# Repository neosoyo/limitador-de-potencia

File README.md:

# Limitador de Potência
Dispositivo para medição de potência e consumo com controlador de limitador de potência para propulsão elétrica de Aeronaves rádio controladas.

# Configurador

Aplicativo para visualização de daods e ajustes da malha de controle.

# Hardware
Utiliza MCU nrf52 (xiao ble), com os seguintes periféricos:

| Periférico | Descrição |
|---|---|
| INA226 | Leitor de corrente, tensão e potência, R shunt de 50mOhms |
| SK6812mini | Led rgba para indicão de status |
| Saída PWM | com BSS138 para ajuste de nível lógico em 5Vdc |
| Entrada PWM | com BSS138 para ajuste de nível lógico para 3.3Vdc |
| Saída UART | 115200 bps, saída de dados em tempo real do control | 
| BLE | Transmissão de informações me tempo real via BLE |

# Firmware

Metas:

* Executar limitação de potência regulando sinal PWM utilizando mensurações do INA226 e uma malha de controle to tipo ADRC.
* Fornecer Potência, Tensão, Corrente, Energia Consumida e sinais PWMs (entrada, controle e saída) pela porta UART.
* Permitir a configuração de número de idenficação e ajuste da malha de controle pela porta USB.
* Através de comunicação bluetooth BLE, transmitir tempo total ligado em segundos, potência máxima, número de identificação e acumulado de energia consumida.
* Suportar bootloader com assinatura de firmware.

# Futuro

Adicionar um monitor de células da bateria: https://www.analog.com/media/en/technical-documentation/data-sheets/ltc6810-1-6810-2.pdf

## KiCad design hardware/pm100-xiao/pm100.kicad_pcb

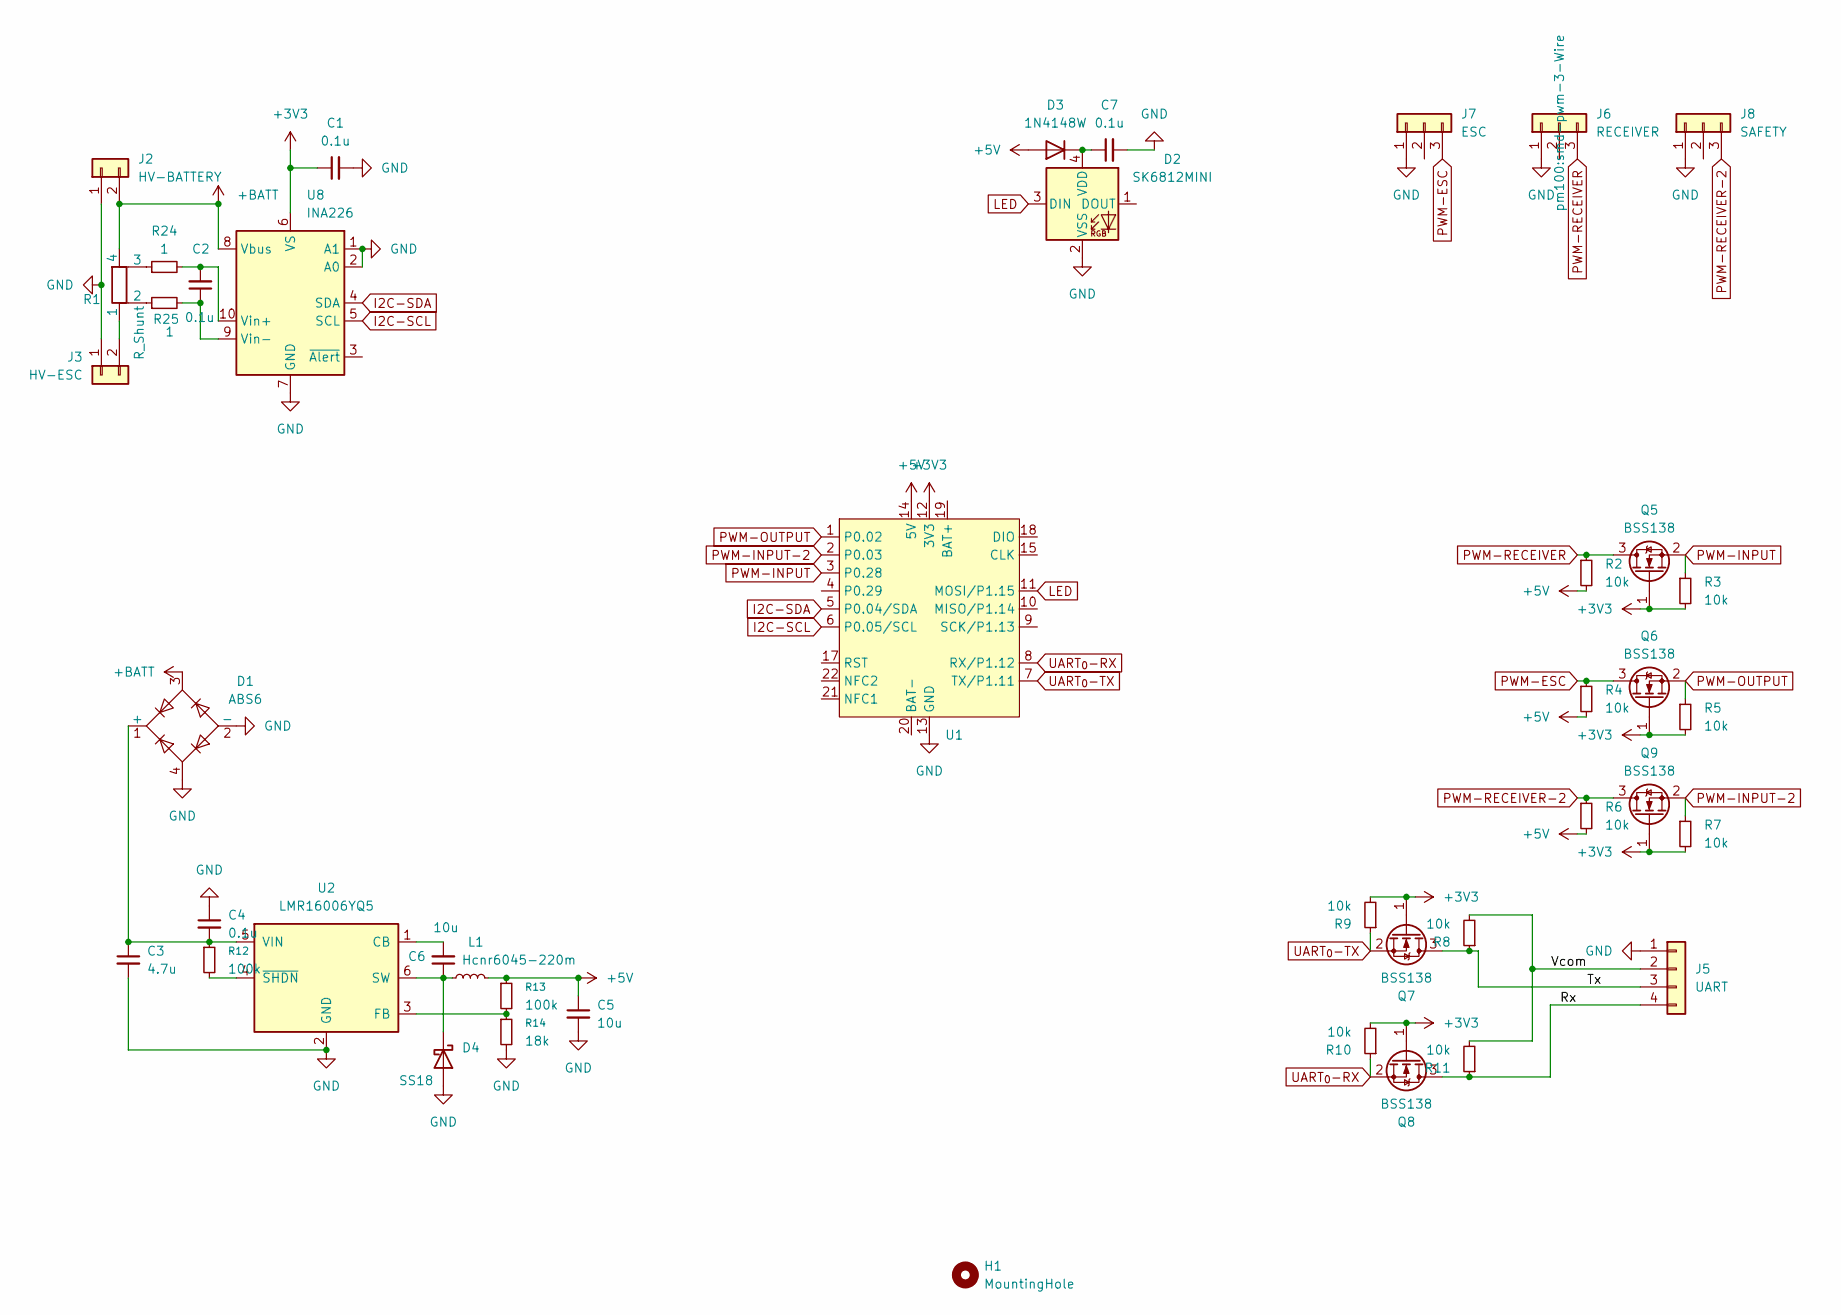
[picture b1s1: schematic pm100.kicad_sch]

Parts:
C1, C2, C7: 0.1u; C_0603_1608Metric
C3: 4.7u; C_0805_2012Metric
C4: 0.1u; C_0805_2012Metric
C5, C6: 10u; C_0805_2012Metric
D1: ABS6; Diode_Bridge_Diotec_ABS
D2: SK6812MINI; SK6812MINI-E
D3: 1N4148W; D_SOD-123
D4: SS18; D_SMA
H1: MountingHole; MountingHole_3.2mm_M3_ISO7380
J2: HV-BATTERY; AMASS_XT60IPW-M_1x03_P7.20mm_Horizontal
J3: HV-ESC; AMASS_XT60PW-F_1x02_P7.20mm_Horizontal
J5: UART; Hirose_DF13-04P-1.25DS_1x04_P1.25mm_Horizontal
J6: RECEIVER; smd-pwm-3-Wire
J7: ESC; smd-pwm-3-Wire
J8: SAFETY; smd-pwm-3-Wire
L1: Hcnr6045-220m; L_Bourns_SRN6045TA
Q5, Q6, Q7, Q8, Q9: BSS138; SOT-23
R1: R_Shunt; MSRSF3920P
R2, R3, R4, R5, R6, R7, R8, R9, R10, R11: 10k; R_0603_1608Metric
R12, R13: 100k; R_0603_1608Metric
R14: 18k; R_0603_1608Metric
R24, R25: 1; R_0603_1608Metric
U1: Xiao_BLE_sense
U2: LMR16006YQ5; SOT-23-6
U8: INA226; VSSOP-10_3x3mm_P0.5mm

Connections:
+3V3: C1.1, Q5.1 (G), Q6.1 (G), Q7.1 (G), Q8.1 (G), Q9.1 (G), R3.2, R5.2, R7.2, R9.2, R10.2, U1.12 (3V3), U8.6 (VS)
+5V: C5.1, D3.2 (A), L1.2, R2.2, R4.2, R6.2, R13.1, U1.14 (5V)
+BATT: D1.3, J2.2, R1.4, U8.8 (Vbus)
/Rx: J5.4, Q8.3 (D), R11.1
/Tx: J5.3, Q7.3 (D), R8.1
/Vcom: J5.2, R8.2, R11.2
GND: C1.2, C3.2, C4.1, C5.2, C7.2, D1.2 (-), D1.4, D2.2 (VSS), D4.2 (A), J2.1, J3.1, J5.1, J6.1, J7.1, J8.1, R14.2, U1.13 (GND), U1.16 (GND), U2.2 (GND), U8.1 (A1), U8.2 (A0), U8.7 (GND)
I2C-SCL: U1.6 (P0.05/SCL), U8.5 (SCL)
I2C-SDA: U1.5 (P0.04/SDA), U8.4 (SDA)
LED: D2.3 (DIN), U1.11 (MOSI/P1.15)
unnamed: C3.1, C4.2, D1.1 (+), R12.1, U2.5 (VIN)
unnamed: C7.1, D2.4 (VDD), D3.1 (K)
unnamed: C6.1, D4.1 (K), L1.1, U2.6 (SW)
unnamed: J3.2, R1.1
unnamed: R1.2, R25.1
unnamed: R1.3, R24.1
unnamed: C6.2, U2.1 (CB)
unnamed: R13.2, R14.1, U2.3 (FB)
unnamed: R12.2, U2.4 (~SHDN)
unnamed: C2.2, R24.2, U8.10 (Vin+)
unnamed: C2.1, R25.2, U8.9 (Vin-)
PWM-ESC: J7.3, Q6.3 (D), R4.1
PWM-INPUT: Q5.2 (S), R3.1, U1.3 (P0.28)
PWM-INPUT-2: Q9.2 (S), R7.1, U1.2 (P0.03)
PWM-OUTPUT: Q6.2 (S), R5.1, U1.1 (P0.02)
PWM-RECEIVER: J6.3, Q5.3 (D), R2.1
PWM-RECEIVER-2: J8.3, Q9.3 (D), R6.1
UART_{0}-RX: Q8.2 (S), R10.1, U1.8 (RX/P1.12)
UART_{0}-TX: Q7.2 (S), R9.1, U1.7 (TX/P1.11)

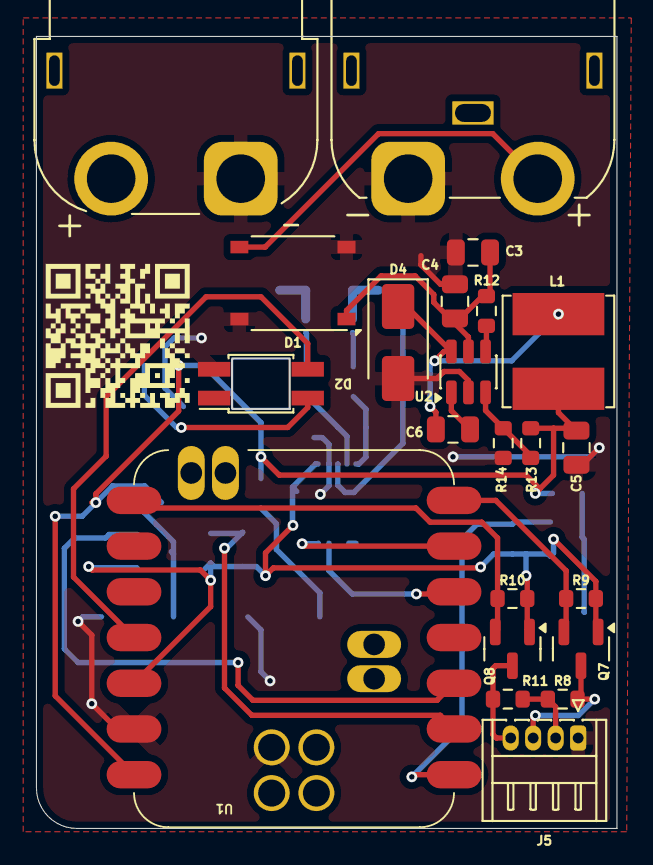
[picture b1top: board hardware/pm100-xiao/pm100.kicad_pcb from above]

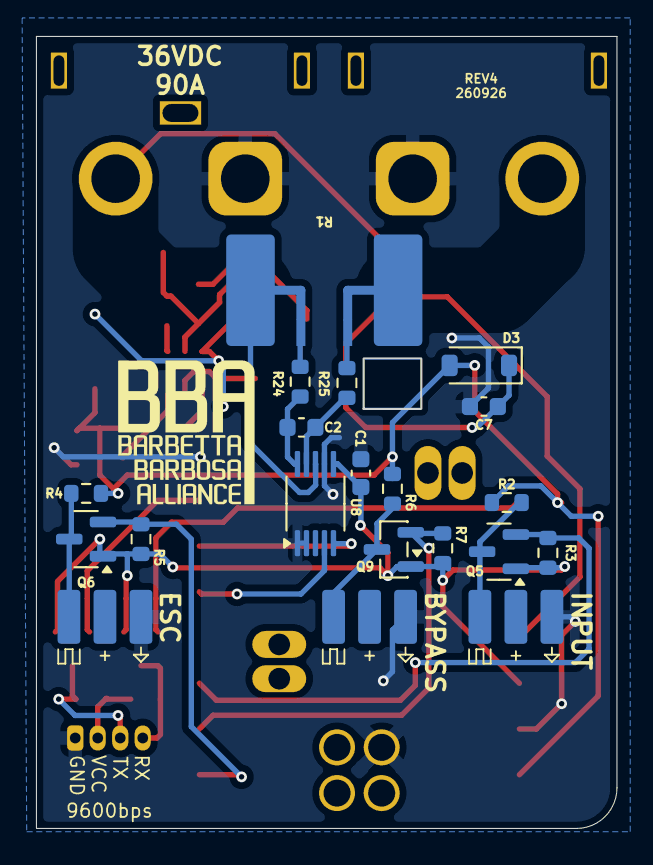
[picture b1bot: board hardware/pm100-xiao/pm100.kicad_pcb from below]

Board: 2 copper layers, 32.2 x 43.9 mm, 42 parts (20 on the bottom side), 29 nets.

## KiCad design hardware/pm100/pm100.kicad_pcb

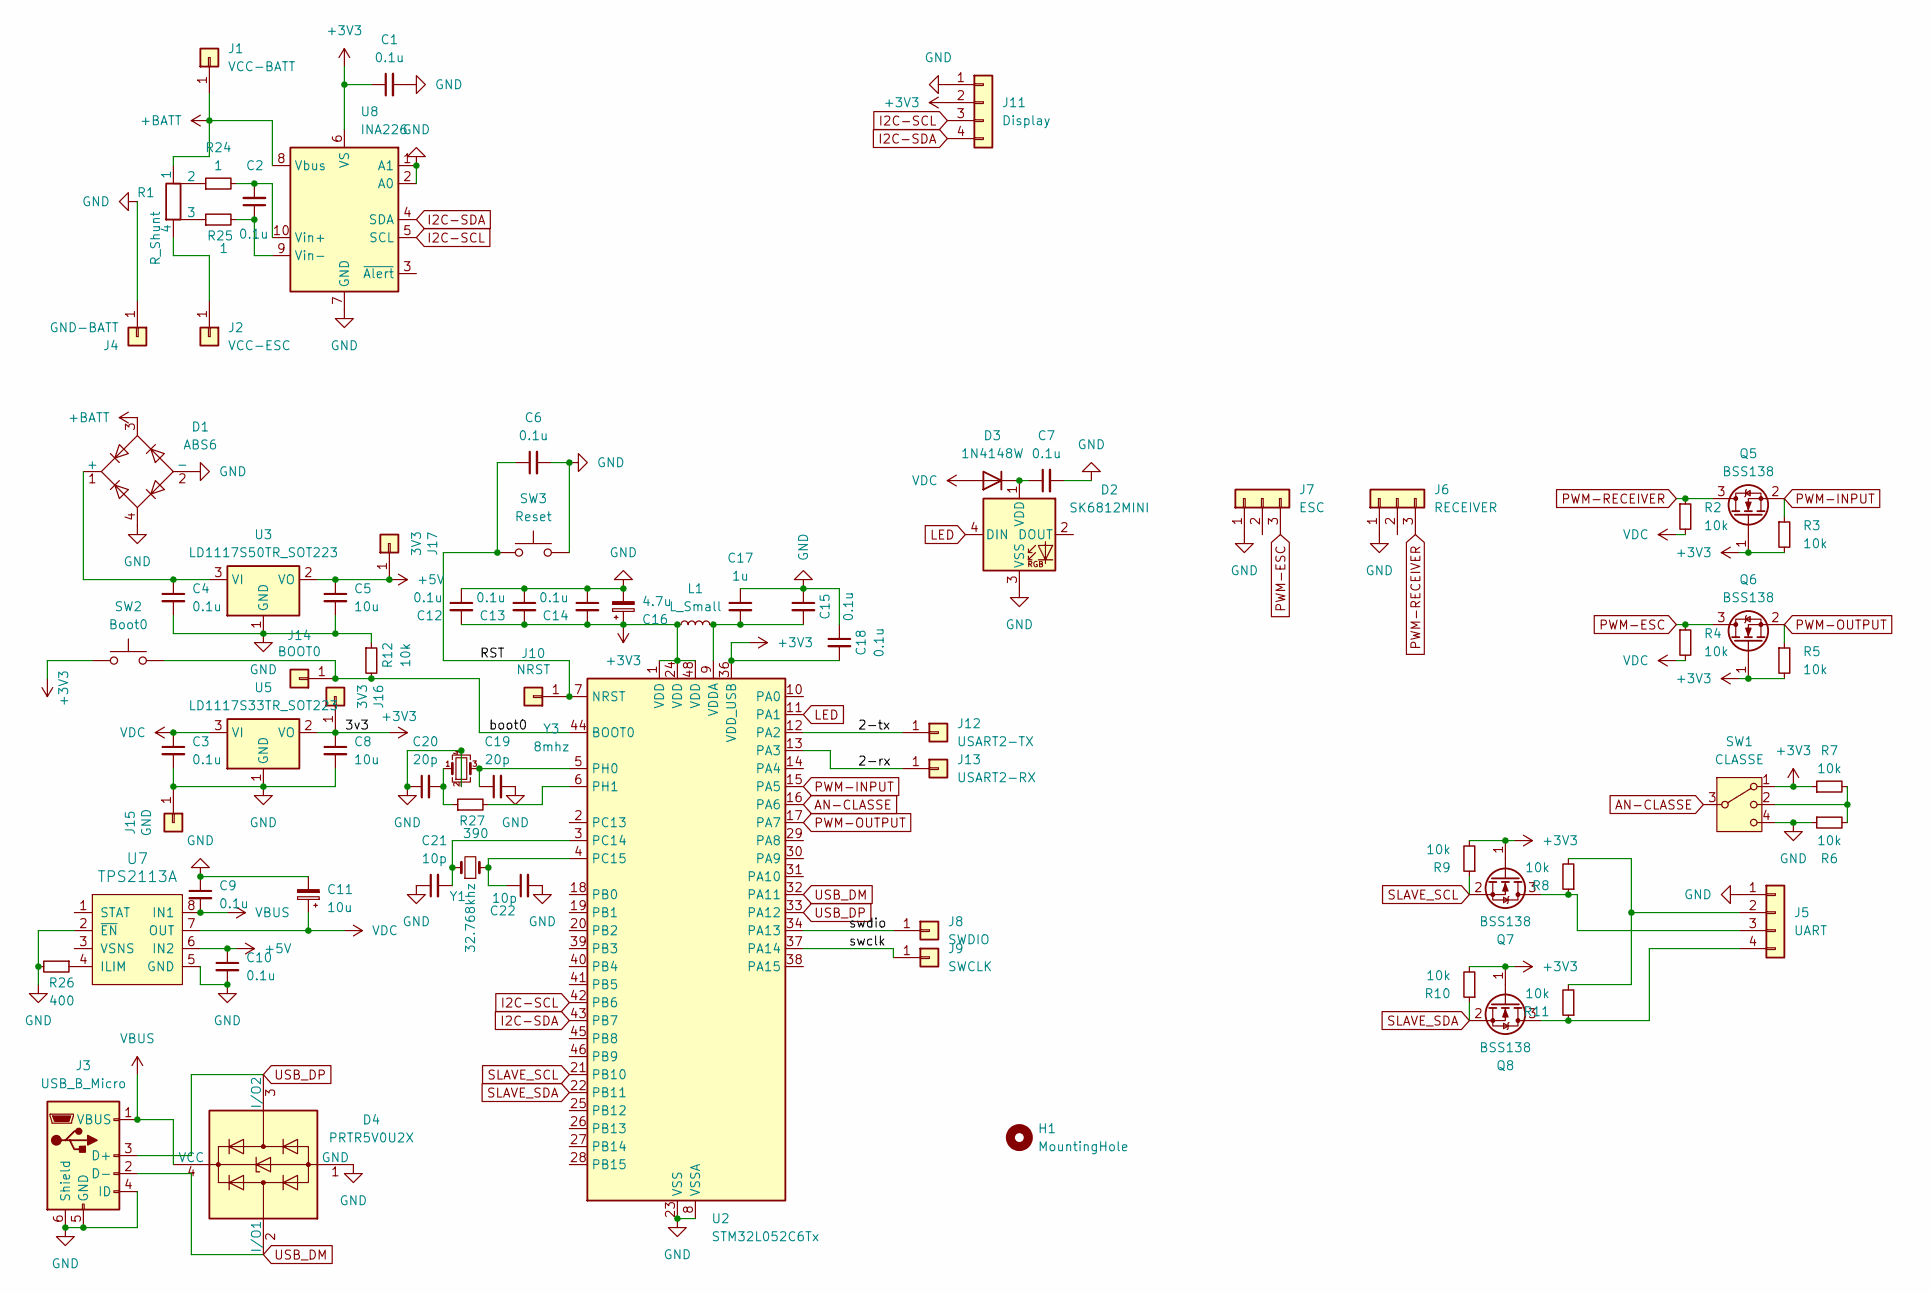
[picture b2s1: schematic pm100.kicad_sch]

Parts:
C1, C2, C3, C4, C6, C7, C9, C10, C12, C13, C14, C15, C18: 0.1u; C_0603_1608Metric
C5, C8: 10u; C_0805_2012Metric
C11: 10u; CP_EIA-3528-21_Kemet-B
C16: 4.7u; CP_EIA-3216-18_Kemet-A
C17: 1u; C_0603_1608Metric
C19, C20: 20p; C_0603_1608Metric
C21, C22: 10p; C_0603_1608Metric
D1: ABS6; Diode_Bridge_Diotec_ABS
D2: SK6812MINI; SK6812MINI-E
D3: 1N4148W; D_SOD-123
D4: PRTR5V0U2X; SOT-143
H1: MountingHole; MountingHole_3.2mm_M3_ISO7380
J1: VCC-BATT; HV_CONN_01x01_pad_6.2x12mm
J2: VCC-ESC; HV_CONN_01x01_pad_6.2x12mm
J3: USB_B_Micro; 47589-1001
J4: GND-BATT; HV_CONN_01x01_pad_6.2x12mm
J5: UART; JST_XH_S4B-XH-A-1_1x04_P2.50mm_Horizontal
J6: RECEIVER; SolderWire_SMD_3
J7: ESC; SolderWire_SMD_3
J8: SWDIO; TestPoint_Pad_D2.0mm
J9: SWCLK; TestPoint_Pad_D2.0mm
J10: NRST; TestPoint_Pad_D2.0mm
J11: Display; OLED_0.91_128x32
J12: USART2-TX; TestPoint_Pad_D2.0mm
J13: USART2-RX; TestPoint_Pad_D2.0mm
J14: BOOT0; TestPoint_Pad_D2.0mm
J15: GND; TestPoint_Pad_D2.0mm
J16, J17: 3V3; TestPoint_Pad_D2.0mm
L1: L_Small; L_0603_1608Metric
Q5, Q6, Q7, Q8: BSS138; SOT-23
R1: R_Shunt; MSRSF3920P
R2, R3, R4, R5, R6, R7, R8, R9, R10, R11, R12: 10k; R_0603_1608Metric
R24, R25: 1; R_0603_1608Metric
R26: 400; R_0603_1608Metric
R27: 390; R_0603_1608Metric
SW1: CLASSE; SW_SP3T_PCM13
SW2: Boot0; SW_Tactile_SPST_NO_Straight_CK_PTS636Sx25SMTRLFS
SW3: Reset; SW_Tactile_SPST_NO_Straight_CK_PTS636Sx25SMTRLFS
U2: STM32L052C6Tx; LQFP-48_7x7mm_P0.5mm
U3: LD1117S50TR_SOT223; SOT-223-3_TabPin2
U5: LD1117S33TR_SOT223; SOT-223-3_TabPin2
U7: TPS2113A; TSSOP-8_3x3mm_P0.65mm
U8: INA226; VSSOP-10_3x3mm_P0.5mm
Y1: 32.768khz; Crystal_SMD_3215-2Pin_3.2x1.5mm
Y3: 8mhz; Crystal_SMD_3225-4Pin_3.2x2.5mm_HandSoldering

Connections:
+3V3: C1.1, C8.1, C12.2, C13.2, C14.2, C16.1, C18.2, J11.2, J16.1, L1.1, Q5.1 (G), Q6.1 (G), Q7.1 (G), Q8.1 (G), R3.2, R5.2, R7.1, R9.2, R10.2, SW1.1, SW2.1, U2.1 (VDD), U2.24 (VDD), U2.36 (VDD_USB), U2.48 (VDD), U5.2 (VO), U8.6 (VS)
+5V: C5.1, C10.1, J17.1, U3.2 (VO), U7.6 (IN2)
+BATT: D1.3, J1.1, R1.1, U8.8 (Vbus)
AN-CLASSE: SW1.3, U2.16 (PA6)
GND: C1.2, C3.2, C4.2, C5.2, C6.2, C7.2, C8.2, C9.1, C10.2, C11.2, C12.1, C13.1, C14.1, C15.1, C16.2, C17.1, C18.1, C19.2, C20.1, C21.1, C22.2, D1.2 (-), D1.4, D2.3 (VSS), D4.1 (GND), J3.4 (ID), J3.5 (GND), J3.6 (Shield), J4.1, J5.1, J6.1, J7.1, J11.1, J15.1, R6.1, R12.1, R26.2, SW1.4, SW3.2, U2.8 (VSSA), U2.23 (VSS), U2.35 (VSS), U2.47 (VSS), U3.1 (GND), U5.1 (GND), U7.2 (~EN), U7.5 (GND), U8.1 (A1), U8.2 (A0), U8.7 (GND), Y3.2, Y3.4
I2C-SCL: J11.3, U2.42 (PB6), U8.5 (SCL)
I2C-SDA: J11.4, U2.43 (PB7), U8.4 (SDA)
LED: D2.4 (DIN), U2.11 (PA1)
unnamed: C20.2, R27.1, Y3.1
unnamed: C4.1, D1.1 (+), U3.3 (VI)
unnamed: C7.1, D2.1 (VDD), D3.1 (K)
unnamed: J2.1, R1.4
unnamed: J5.2, R8.2, R11.2
unnamed: J5.3, Q7.3 (D), R8.1
unnamed: J5.4, Q8.3 (D), R11.1
unnamed: J8.1, U2.34 (PA13)
unnamed: J9.1, U2.37 (PA14)
unnamed: C6.1, J10.1, SW3.1, U2.7 (NRST)
unnamed: J12.1, U2.12 (PA2)
unnamed: J13.1, U2.13 (PA3)
unnamed: J14.1, R12.2, SW2.2, U2.44 (BOOT0)
unnamed: R1.2, R24.1
unnamed: R1.3, R25.1
unnamed: R6.2, R7.2, SW1.2
unnamed: C21.2, U2.3 (PC14), Y1.1
unnamed: C22.1, U2.4 (PC15), Y1.2
unnamed: C19.1, U2.5 (PH0), Y3.3
unnamed: R27.2, U2.6 (PH1)
unnamed: C15.2, C17.2, L1.2, U2.9 (VDDA)
unnamed: R26.1, U7.4 (ILIM)
unnamed: C2.2, R24.2, U8.10 (Vin+)
unnamed: C2.1, R25.2, U8.9 (Vin-)
PWM-ESC: J7.3, Q6.3 (D), R4.1
PWM-INPUT: Q5.2 (S), R3.1, U2.15 (PA5)
PWM-OUTPUT: Q6.2 (S), R5.1, U2.17 (PA7)
PWM-RECEIVER: J6.3, Q5.3 (D), R2.1
SLAVE_SCL: Q7.2 (S), R9.1, U2.21 (PB10)
SLAVE_SDA: Q8.2 (S), R10.1, U2.22 (PB11)
USB_DM: D4.2 (I/O1), J3.2 (D-), U2.32 (PA11)
USB_DP: D4.3 (I/O2), J3.3 (D+), U2.33 (PA12)
VBUS: C9.2, D4.4 (VCC), J3.1 (VBUS), U7.8 (IN1)
VDC: C3.1, C11.1, D3.2 (A), R2.2, R4.2, U5.3 (VI), U7.7 (OUT)

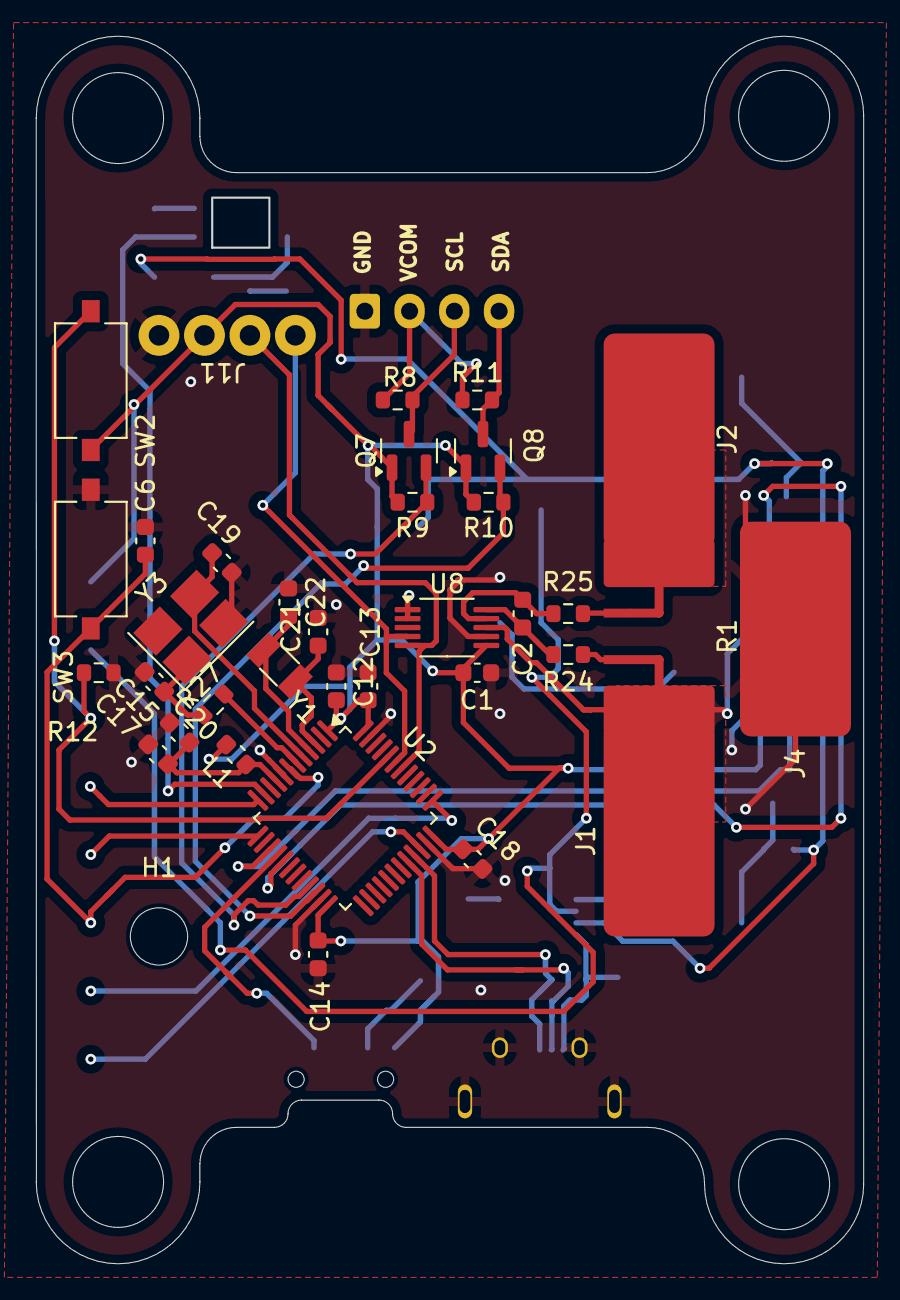
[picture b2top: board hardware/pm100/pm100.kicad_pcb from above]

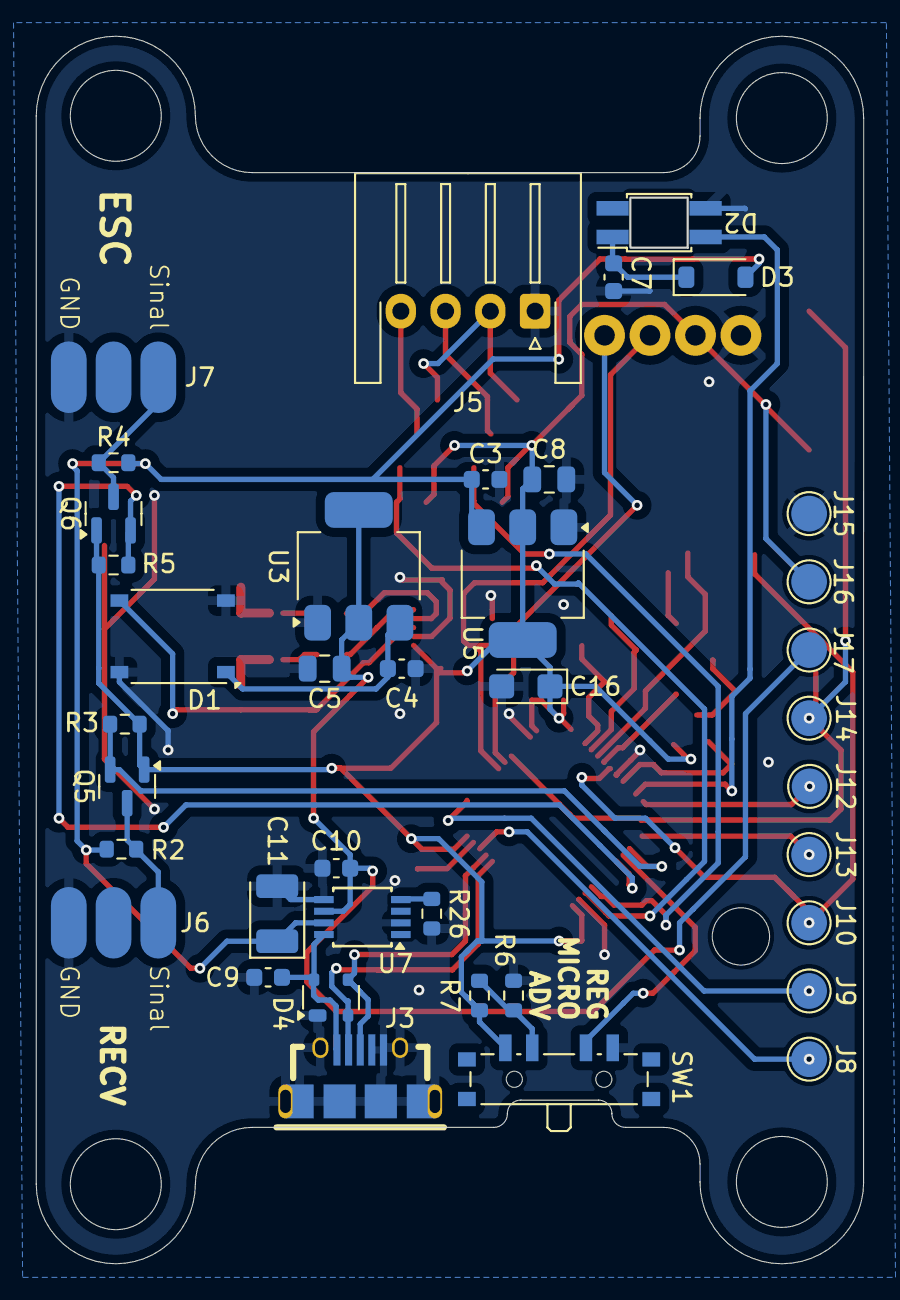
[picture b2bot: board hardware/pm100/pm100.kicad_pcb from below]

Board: 2 copper layers, 46.2 x 68.5 mm, 75 parts (39 on the bottom side), 42 nets.

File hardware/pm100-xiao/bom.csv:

"Reference","Value","Datasheet","Footprint","Qty","DNP"
"C1,C2,C3,C4,C7,C9,C10,C12,C13,C14,C15,C18","0.1u","~","Capacitor_SMD:C_0603_1608Metric","12",""
"C5,C8,C11","10u","~","-- mixed values --","3",""
"C16","4.7u","~","Capacitor_Tantalum_SMD:CP_EIA-3216-18_Kemet-A","1",""
"C17","1u","~","Capacitor_SMD:C_0603_1608Metric","1",""
"C19,C20","20p","~","Capacitor_SMD:C_0603_1608Metric","2",""
"C21,C22","10p","~","Capacitor_SMD:C_0603_1608Metric","2",""
"D1","ABS6","https://diotec.com/tl_files/diotec/files/pdf/datasheets/abs2.pdf","Diode_SMD:Diode_Bridge_Diotec_ABS","1",""
"D2","SK6812MINI","https://cdn-shop.adafruit.com/product-files/2686/SK6812MINI_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","Sigma Footprints:SK6812MINI-E","1",""
"D3","1N4148W","https://www.vishay.com/docs/85748/1n4148w.pdf","Diode_SMD:D_SOD-123","1",""
"D4","PRTR5V0U2X","https://assets.nexperia.com/documents/data-sheet/PRTR5V0U2X.pdf","Package_TO_SOT_SMD:SOT-143","1",""
"J1","VCC-BATT","~","footprints:HV_CONN_01x01_pad_6.2x12mm","1",""
"J2","VCC-ESC","~","footprints:HV_CONN_01x01_pad_6.2x12mm","1",""
"J3","USB_B_Micro","~","footprints:47589-1001","1",""
"J4","GND-BATT","~","footprints:HV_CONN_01x01_pad_6.2x12mm","1",""
"J5","UART","~","Connector_JST:JST_XH_S4B-XH-A-1_1x04_P2.50mm_Horizontal","1",""
"J6","RECEIVER","~","Sigma Footprints:SolderWire_SMD_3","1",""
"J7","ESC","~","Sigma Footprints:SolderWire_SMD_3","1",""
"J8","SWDIO","~","TestPoint:TestPoint_Pad_D2.0mm","1",""
"J9","SWCLK","~","TestPoint:TestPoint_Pad_D2.0mm","1",""
"J10","NRST","~","TestPoint:TestPoint_Pad_D2.0mm","1",""
"J11","Display","~","Sigma Footprints:OLED_0.91_128x32","1",""
"J12","USART2-TX","~","TestPoint:TestPoint_Pad_D2.0mm","1",""
"J13","USART2-RX","~","TestPoint:TestPoint_Pad_D2.0mm","1",""
"J14","BOOT0","~","TestPoint:TestPoint_Pad_D2.0mm","1",""
"L1","L_Small","~","Inductor_SMD:L_0603_1608Metric","1",""
"Q5,Q6,Q7,Q8","BSS138","https://www.onsemi.com/pub/Collateral/BSS138-D.PDF","Package_TO_SOT_SMD:SOT-23","4",""
"R1","R_Shunt","~","footprints:MSRSF3920P","1",""
"R2,R3,R4,R5,R6,R7,R8,R9,R10,R11,R12","10k","~","Resistor_SMD:R_0603_1608Metric","11",""
"R24,R25","1","~","Resistor_SMD:R_0603_1608Metric","2",""
"R26","400","~","Resistor_SMD:R_0603_1608Metric","1",""
"R27","390","~","Resistor_SMD:R_0603_1608Metric","1",""
"SW1","CLASSE","~","Button_Switch_SMD:SW_SP3T_PCM13","1",""
"U2","STM32L052C6Tx","https://www.st.com/resource/en/datasheet/stm32l052c6.pdf","Package_QFP:LQFP-48_7x7mm_P0.5mm","1",""
"U3","LD1117S50TR_SOT223","http://www.st.com/st-web-ui/static/active/en/resource/techni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","Package_TO_SOT_SMD:SOT-223-3_TabPin2","1",""
"U5","LD1117S33TR_SOT223","http://www.st.com/st-web-ui/static/active/en/resource/techni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","Package_TO_SOT_SMD:SOT-223-3_TabPin2","1",""
"U7","TPS2113A","https://www.ti.com/lit/ds/symlink/tps2113a.pdf?ts=1597267193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","Package_SO:TSSOP-8_3x3mm_P0.65mm","1",""
"U8","INA226","http://www.ti.com/lit/ds/symlink/ina226.pdf","Package_SO:VSSOP-10_3x3mm_P0.5mm","1",""
"Y1","32.768khz","~","Crystal:Crystal_SMD_3215-2Pin_3.2x1.5mm","1",""
"Y2","8mhz","~","Crystal:Crystal_SMD_3215-2Pin_3.2x1.5mm","1",""

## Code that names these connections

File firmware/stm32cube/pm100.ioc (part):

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Mcu.Name=STM32L052C(6-8)Tx
Mcu.Package=LQFP48
Mcu.UserName=STM32L052C6Tx
PA1.GPIOParameters=GPIO_Label
PA1.GPIO_Label=LED
PA1.Signal=GPIO_Output
PA11.Mode=Device
PA11.Signal=USB_DM
PA12.Mode=Device
PA12.Signal=USB_DP
PA5.GPIOParameters=GPIO_Label
PA5.GPIO_Label=PWM_INPUT
PA5.Signal=S_TIM2_CH1
PA6.GPIOParameters=GPIO_Label
PA6.GPIO_Label=CLASS_SELECTOR
PA6.Mode=IN6
PA6.Signal=ADC_IN6
PA7.GPIOParameters=GPIO_Label
PA7.GPIO_Label=PWM_OUTPUT
PA7.Signal=S_TIM22_CH2
PB10.GPIOParameters=GPIO_Label
PB10.GPIO_Label=I2C2_SCL_SLAVE
PB10.Mode=I2C
PB10.Signal=I2C2_SCL
PB11.GPIOParameters=GPIO_Label
PB11.GPIO_Label=I2C2_SDA_SLAVE
PB11.Mode=I2C
PB11.Signal=I2C2_SDA
PB6.Mode=I2C
PB6.Signal=I2C1_SCL
PB7.Mode=I2C
PB7.Signal=I2C1_SDA
RCC.HSE_VALUE=8000000
RCC.SYSCLKFreq_VALUE=2097000
board=custom

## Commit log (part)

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2025-04-02 reiniciando projeto
2025-04-02 adicionado projeto do stm32cubemx com pinagem e periféricos declarados
2025-04-03 adicionado GND no cristal de 8mhz
2026-03-16 usando Xiao Ble
2026-03-23 last revision
2026-05-22 troca de arquitetura de stm para nrf52 e uso de Zephyr para o firmware
2026-05-22 removendo submodule projeto pm100
2026-05-22 atualizando readme e adicionando arquivos 3ds do hardware
2026-05-22 ajustando pinagem LED RGBA
2026-05-22 Update README.md
    anotações extras
